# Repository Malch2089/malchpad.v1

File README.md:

# malchpad.v1
it contains pcb and case designs of my malchpad which a small functional 6 keys keyboard

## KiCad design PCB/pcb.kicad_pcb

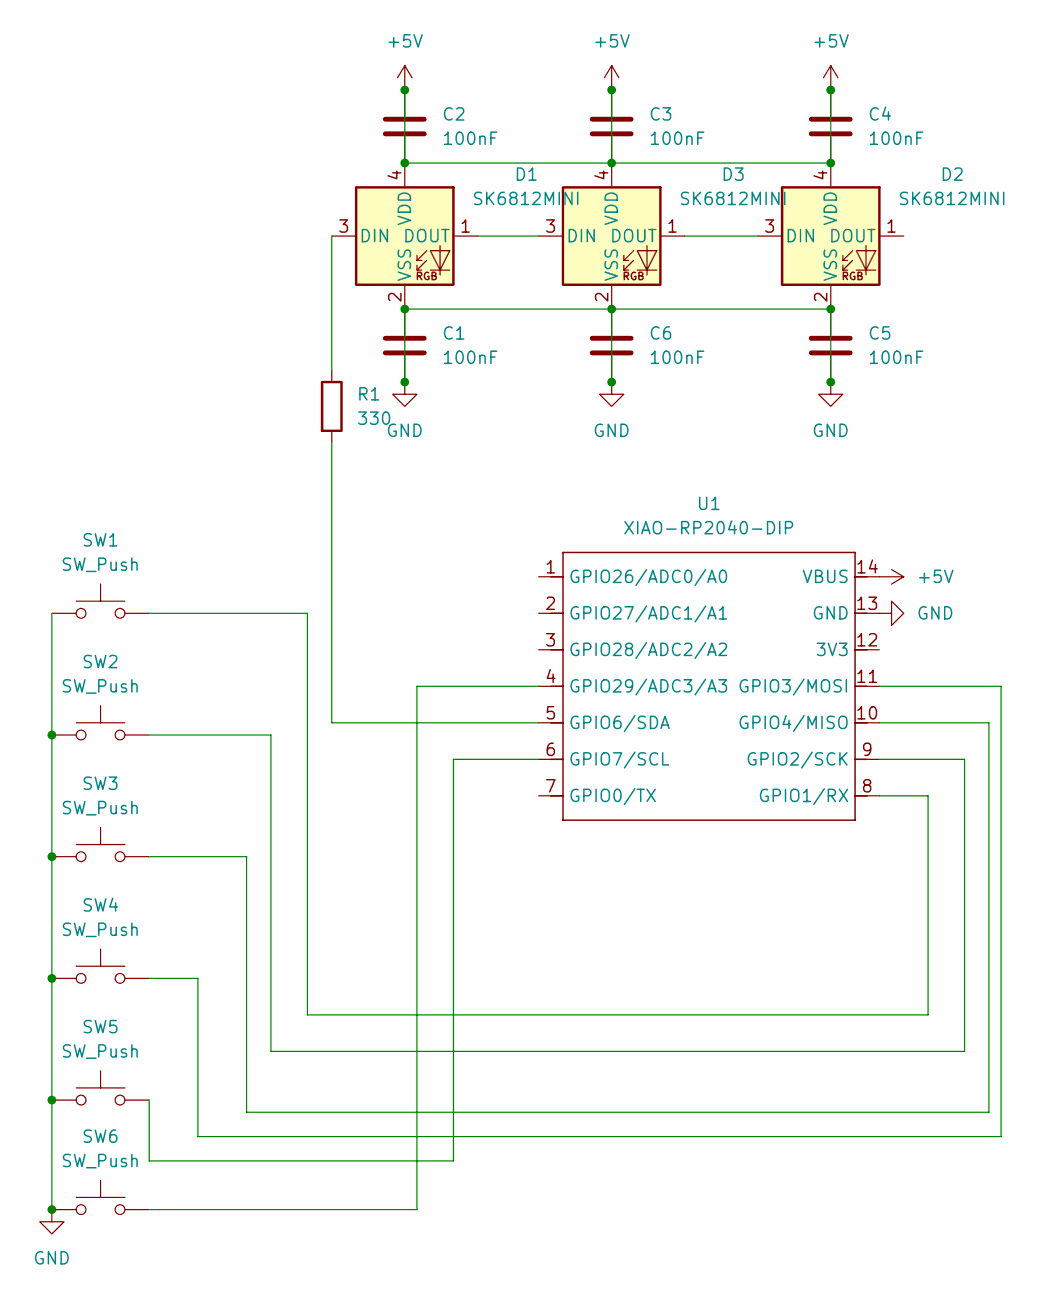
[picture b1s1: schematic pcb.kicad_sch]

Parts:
C1, C2, C3, C4, C5, C6: 100nF; C_0603_1608Metric
D1, D2, D3: SK6812MINI; LED_SK6812MINI_PLCC4_3.5x3.5mm_P1.75mm
R1: 330; R_0603_1608Metric
SW1, SW2, SW3, SW4, SW5, SW6: SW_Push; SW_Cherry_MX_1.00u_PCB
U1: XIAO-RP2040-DIP

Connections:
+5V: C2.1, C2.2, C3.1, C3.2, C4.1, C4.2, D1.4 (VDD), D2.4 (VDD), D3.4 (VDD), U1.14 (VBUS)
GND: C1.1, C1.2, C5.1, C5.2, C6.1, C6.2, D1.2 (VSS), D2.2 (VSS), D3.2 (VSS), SW1.1, SW2.1, SW3.1, SW4.1, SW5.1, SW6.1, U1.13 (GND)
unnamed: D1.3 (DIN), R1.1
unnamed: D1.1 (DOUT), D3.3 (DIN)
unnamed: D2.3 (DIN), D3.1 (DOUT)
unnamed: SW1.2, U1.8 (GPIO1/RX)
unnamed: SW2.2, U1.9 (GPIO2/SCK)
unnamed: SW4.2, U1.11 (GPIO3/MOSI)
unnamed: SW3.2, U1.10 (GPIO4/MISO)
unnamed: R1.2, U1.5 (GPIO6/SDA)
unnamed: SW5.2, U1.6 (GPIO7/SCL)
unnamed: SW6.2, U1.4 (GPIO29/ADC3/A3)

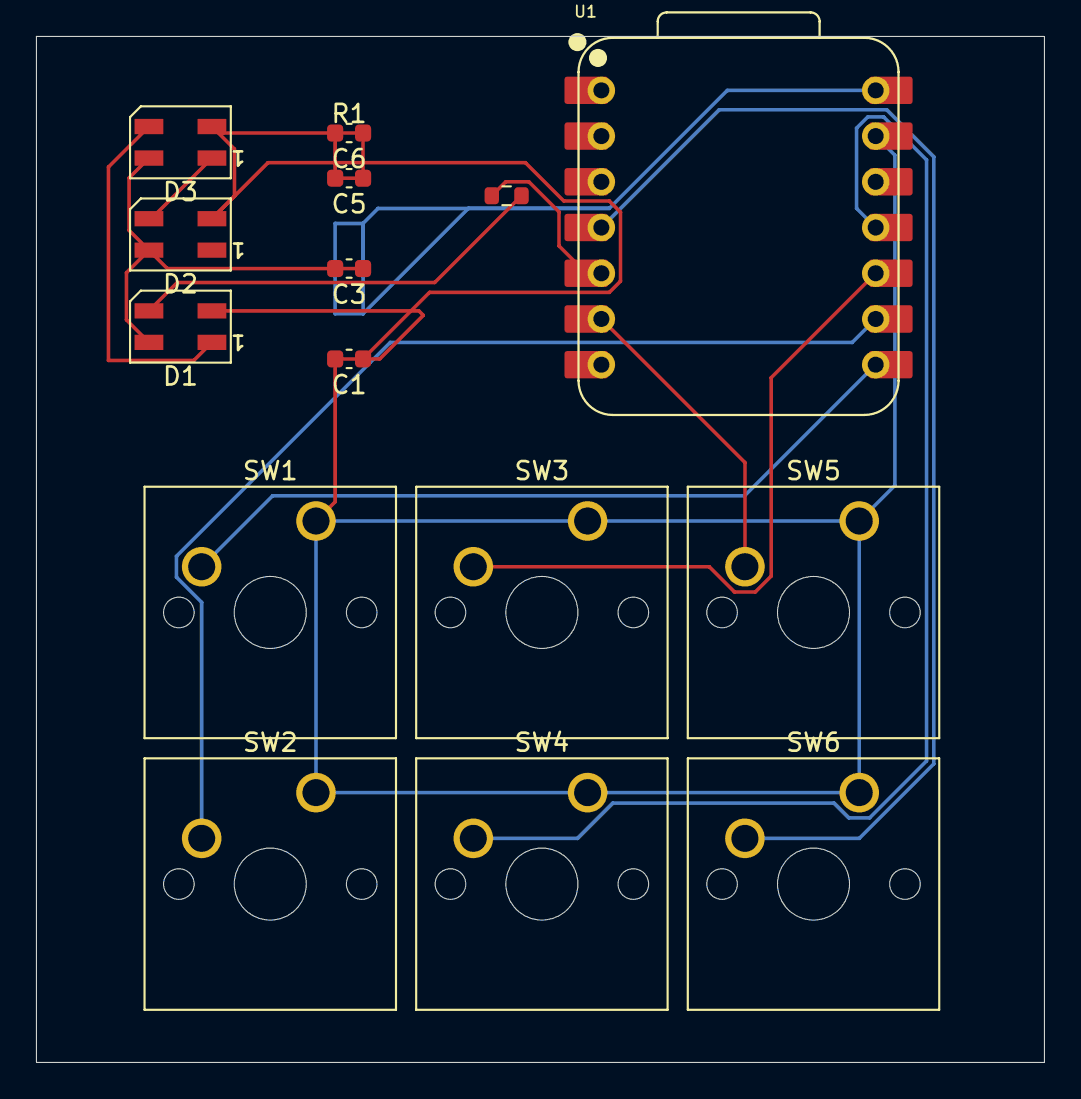
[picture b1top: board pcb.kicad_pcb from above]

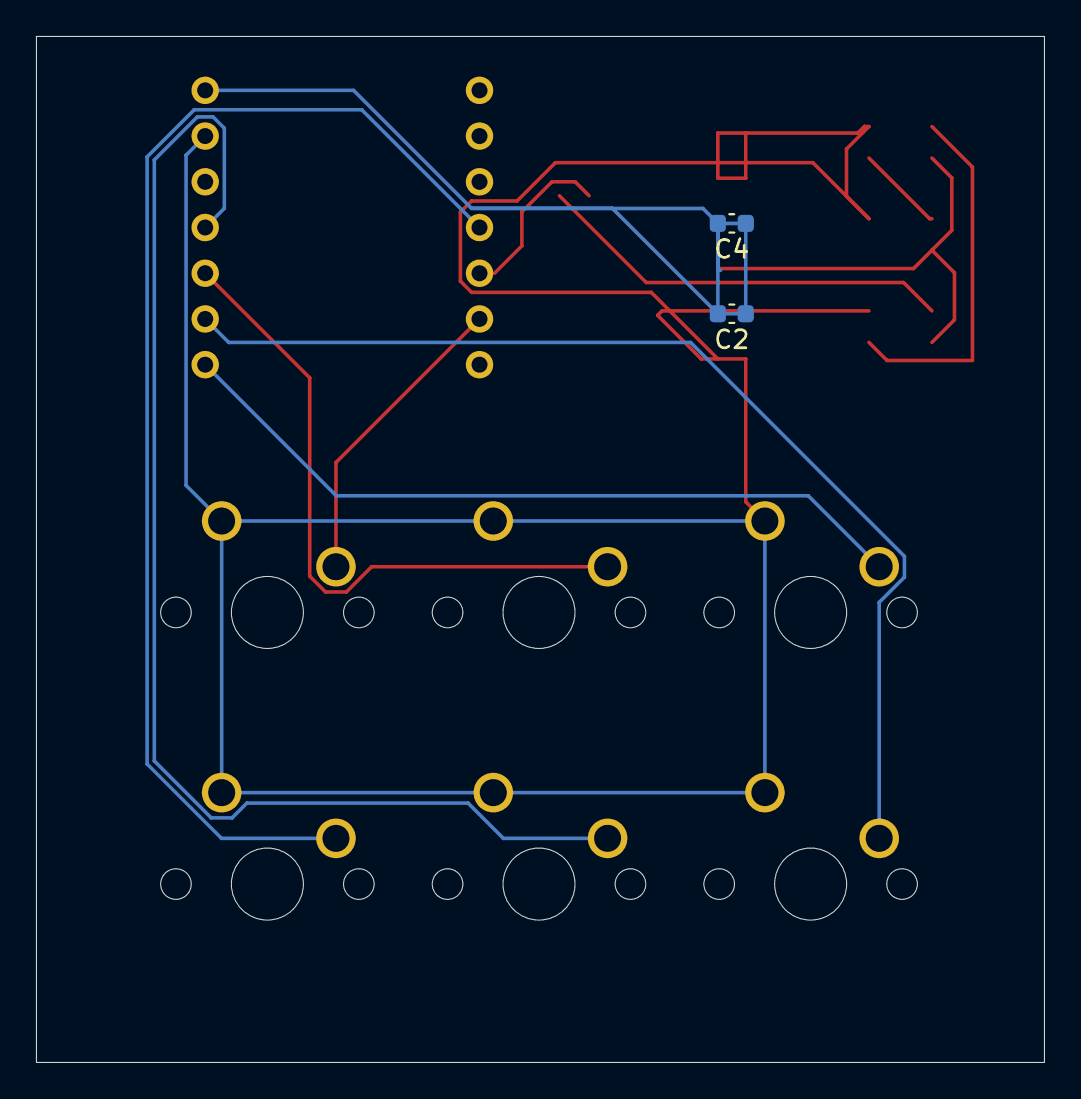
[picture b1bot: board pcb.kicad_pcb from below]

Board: 2 copper layers, 56.0 x 57.0 mm, 17 parts (2 on the bottom side), 12 nets.

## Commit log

2026-01-22 Add project files
2026-05-06 Add images to README for visual reference
    Added images to enhance README documentation.
